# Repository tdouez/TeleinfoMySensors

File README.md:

# TeleinfoMySensors v2.1.0

Interface Téléinfo pour compteur Linky avec MySensors - version compatible mode standard et historique

Projet utilisant un Arduino Pro micro et un module NRF24L01

- Hardware disponible sur https://www.openhardware.io/view/744/MySensors-Linky
- Boîtier disponible sur https://www.thingiverse.com/thing:3985437
- Description disponible sur http://fumeebleue.fr

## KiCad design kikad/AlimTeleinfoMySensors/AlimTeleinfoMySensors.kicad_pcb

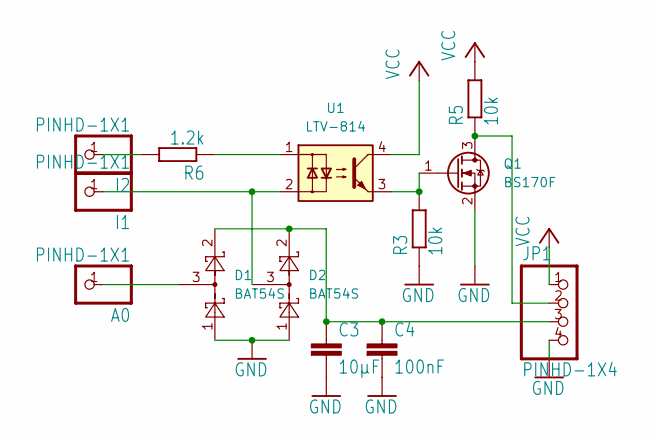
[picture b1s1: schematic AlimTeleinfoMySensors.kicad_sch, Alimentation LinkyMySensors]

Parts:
A0: PINHD-1X1; 1X01
C3: 10µF; C_1210_3225Metric
C4: 100nF; C_1206_3216Metric
D1, D2: BAT54S; SOT-23
I1, I2: PINHD-1X1; 1X01
JP1: PINHD-1X4; 1X04
Q1: BS170F; SOT-23
R3, R5: 10k; R_1206_3216Metric
R6: 1.2k; R_1206_3216Metric
U1: LTV-814; DIP-4_W7.62mm

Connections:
GND: C3.2, C4.2, D1.1, D2.1, JP1.4, Q1.2 (S), R3.1
unnamed: A0.1, D1.3
unnamed: C3.1, C4.1, D1.2, D2.2, JP1.3
unnamed: D2.3, I1.1, U1.2
unnamed: I2.1, R6.2
unnamed: JP1.2, Q1.3 (D), R5.1
unnamed: Q1.1 (G), R3.2, U1.3
unnamed: R6.1, U1.1
VCC: JP1.1, R5.2, U1.4

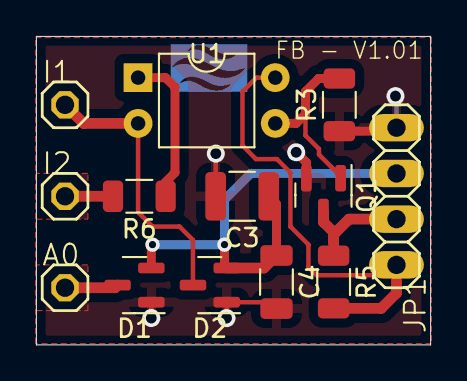
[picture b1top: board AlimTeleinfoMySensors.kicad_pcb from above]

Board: 2 copper layers, 21.9 x 17.1 mm, 14 parts (0 on the bottom side), 9 nets.

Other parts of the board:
U$1: FB

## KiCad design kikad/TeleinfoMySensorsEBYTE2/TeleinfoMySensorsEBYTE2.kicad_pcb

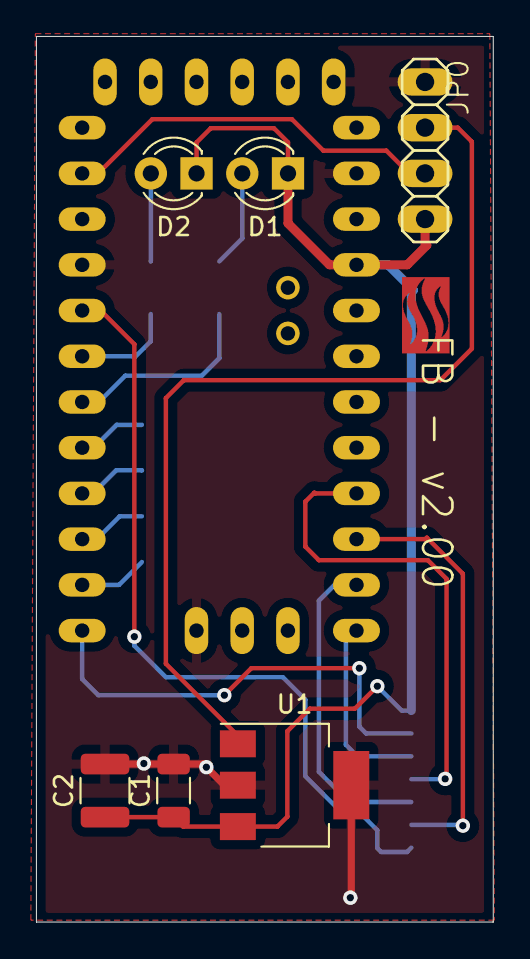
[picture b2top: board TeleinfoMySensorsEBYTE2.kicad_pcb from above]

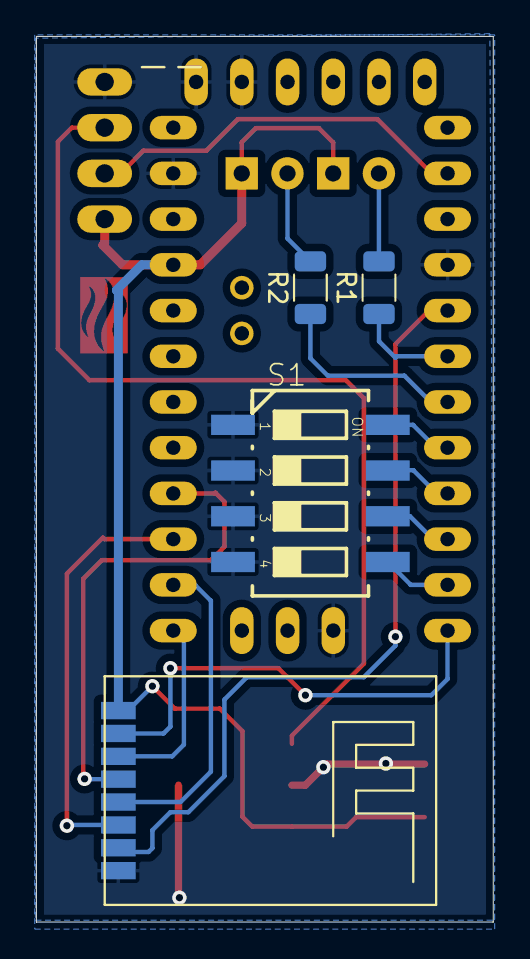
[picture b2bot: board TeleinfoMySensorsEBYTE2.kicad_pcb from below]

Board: 2 copper layers, 25.4 x 49.2 mm, 12 parts (5 on the bottom side), 18 nets.

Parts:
C1: 100nF; C_1206_3216Metric
C2: 10µF; C_1210_3225Metric
D1, D2: LED; LED_D3.0mm
JP0: PINHD-1X4; 1X04
R1, R2: 1.2k; R_1206_3216Metric
S1: 219-04; CTS-219-04
U1: MCP1703A-3302_SOT223; SOT-223-3_TabPin2
U$1: ABK-PRO-MINI
U$4: FB
U$5: NRFL01SMSEBYTE; 24L01SMDEBYTE

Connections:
GND: C1.2, C2.2, JP0.1, S1.1, S1.2, S1.3, S1.4, U1.2 (GND), U$1.GND, U$1.GND1 (GND2), U$1.GND2 (GND3), U$1.GND3 (GND4), U$1.GND4 (GND1), U$5.GND
unnamed: C1.1, C2.1, D1.1 (K), D2.1 (K), JP0.4, U1.3 (VO), U$1.VCC, U$5.3.3 (VDD)
unnamed: JP0.2, U1.1 (VI)
unnamed: JP0.3, U$1.RX1
unnamed: R1.1, U$1.D3
unnamed: D2.2 (A), R1.2
unnamed: R2.1, U$1.D4
unnamed: D1.2 (A), R2.2
unnamed: S1.5, U$1.D8
unnamed: S1.6, U$1.D7
unnamed: S1.7, U$1.D6
unnamed: S1.8, U$1.D5
unnamed: U$1.D2, U$5.IRQ
unnamed: U$1.D9, U$5.CE
unnamed: U$1.D10, U$5.CSN
unnamed: U$1.D11, U$5.MOSI
unnamed: U$1.D12, U$5.MISO
unnamed: U$1.D13, U$5.SCK

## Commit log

2019-12-16 Create eagle
2019-12-16 Create t
2020-04-23 Add files via upload
    ADCO bug fix
2020-04-25 ADCO bug fix
    ADCO bug fix
2020-04-25 V1.1.0 compatible mode standard
2020-04-26 info data
2020-04-26 dev 26
2020-04-28 V1.1.0
    Version mode standard Linky
2020-08-21 V1.1.1
    V1.1.1
2020-08-26 V1.1.2
    - Ajout delais sur presentation et send, afin de soulager la gateway
    - Envoi données producteur et triphasé si besoin
    - Correction sur send EASF et EADS en WH au lieu du VA
2020-09-01 1.1.2
    - Ajout delais sur presentation et send, afin de soulager la gateway
    - Envoi données producteur et triphasé si besoin
    - Correction sur send EASF et EADS en WH au lieu du VA
    - Accents retirés sur les libellés de présentation
2020-10-23 options reglages NRF24L01
    Ajout options reglages NRF24L01 (puissance, débit, canal)
2020-10-26 1.1.4
    Optimisation bug fix
2021-05-12 1.1.5
    Correction erreur de compil et optimisation
2021-09-09 Fix display on entites on home assistant cf: https://www.home-assistant.io/integrations/sensor.mysensors/
2021-09-23 Create LICENSE
2021-09-24 Add node REPEATER
2021-09-26 Fix unit Wh from kwh send to controller
2021-10-05 Ajout prefixes et corrections sur type de compteur
    Ajout prefixes et corrections sur type de compteur
2022-06-24 V2.0.0
    Utilisation librairie universelle LibTeleinfo modifiée (pas d'enregistrement, pas assez de RAM sur l'ATmega328 pour avoir une solution stable en TIC full)
    Compatible mode historique et mode standard; détermination automatique au démarrage
    Attention tous les commandes MySensors ont été revues (n° différent pour certaines)
2022-09-27 v2.0.1
    Correction sur détection TIC standard
2022-12-20 2.0.3
    Kicad PCB with DIP switch
2023-01-27 v2.0.2
    Correction sur l'envoi des prefixes des chil_id_smax. Merci à Laurent B.
2023-02-02 V2.0.3
    Mise à jour librairie LibTeleinfo v1.1.5 avec derniers correctifs https://github.com/hallard/LibTeleinfo/releases
2023-02-27 v2.0.4
    Correction sur l'envoi des préfixes CHILD_ID_CCA*
2023-03-06 V2.0.5
    Optimisation mémoire
2023-04-17 v2.0.6
    Ajout temps maj pour éviter le spam de la gateway et contrôle étiquette BASE
2023-05-04 v2.0.7
    Amélioration détection mod eTIC historique/standard
2023-06-03 V2.0.8
    Correction detection TIC historique
2023-06-14 v2.0.9
    Ajout compatibilité Arduino pro micro et correction detection TIC historique
2023-06-15 v2.1.0
    Modification mise à jour gateway, plus de spam ni de perte d'étiquette.
    Code optimisé pour l'arduino pro micro ATMEGA32u4
